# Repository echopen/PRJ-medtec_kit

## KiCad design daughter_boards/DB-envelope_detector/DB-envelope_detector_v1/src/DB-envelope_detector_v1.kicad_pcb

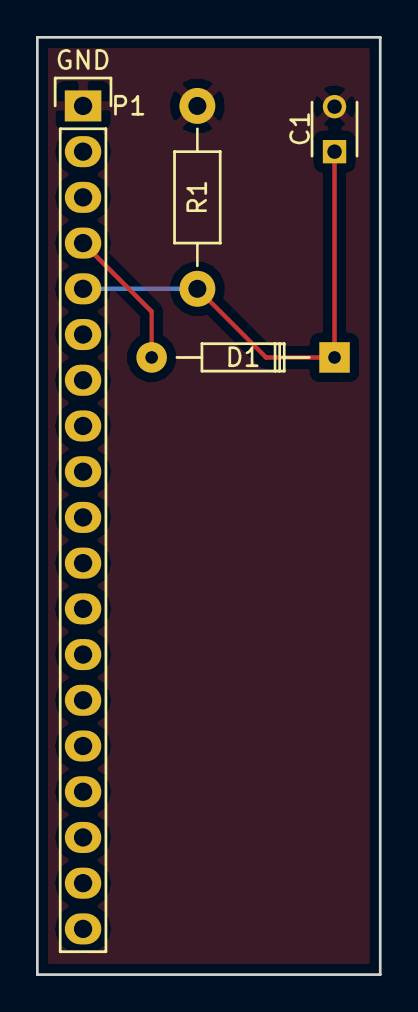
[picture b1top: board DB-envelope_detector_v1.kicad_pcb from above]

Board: 2 copper layers, 19.0 x 52.1 mm, 4 parts (0 on the bottom side), 3 nets.

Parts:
C1: 10p; C_Disc_D3_P2.5
D1: 1N60; Diode_DO-35_SOD27_Horizontal_RM10
P1: CONN_01X19; Header_pin_angled_1x19
R1: 3.9k; Resistor_Horizontal_RM10mm

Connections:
GND: C1.2, P1.1, R1.2
unnamed: C1.1, D1.1, P1.5, R1.1
unnamed: D1.2, P1.4

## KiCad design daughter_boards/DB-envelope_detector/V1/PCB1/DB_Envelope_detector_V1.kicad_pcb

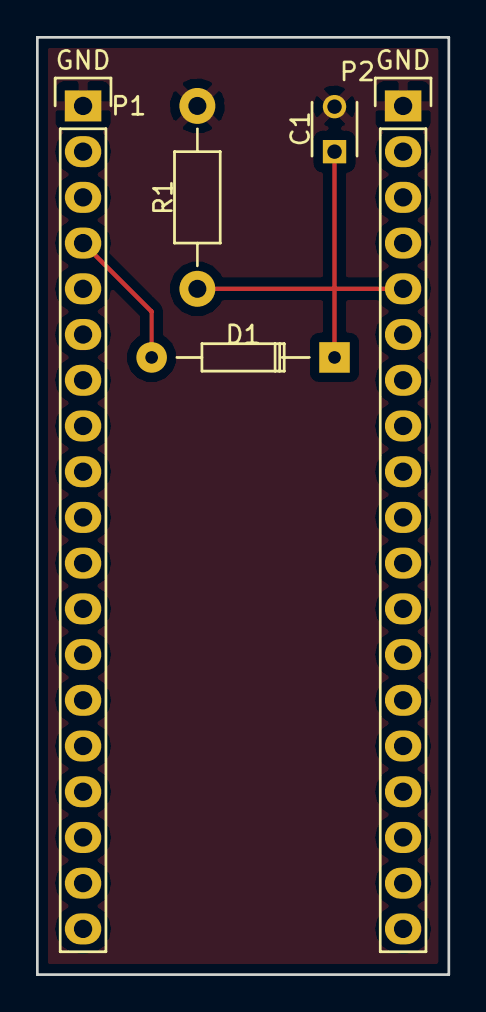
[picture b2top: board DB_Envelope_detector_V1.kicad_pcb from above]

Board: 2 copper layers, 22.9 x 52.1 mm, 5 parts (0 on the bottom side), 3 nets.

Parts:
C1: 10p; C_Disc_D3_P2.5
D1: 1N60; Diode_DO-35_SOD27_Horizontal_RM10
P1, P2: CONN_01X19; Header_pin_1x19
R1: 3.9k; Resistor_Horizontal_RM10mm

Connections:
GND: C1.2, P1.1, P2.1, R1.2
unnamed: C1.1, D1.1, P2.5, R1.1
unnamed: D1.2, P1.4

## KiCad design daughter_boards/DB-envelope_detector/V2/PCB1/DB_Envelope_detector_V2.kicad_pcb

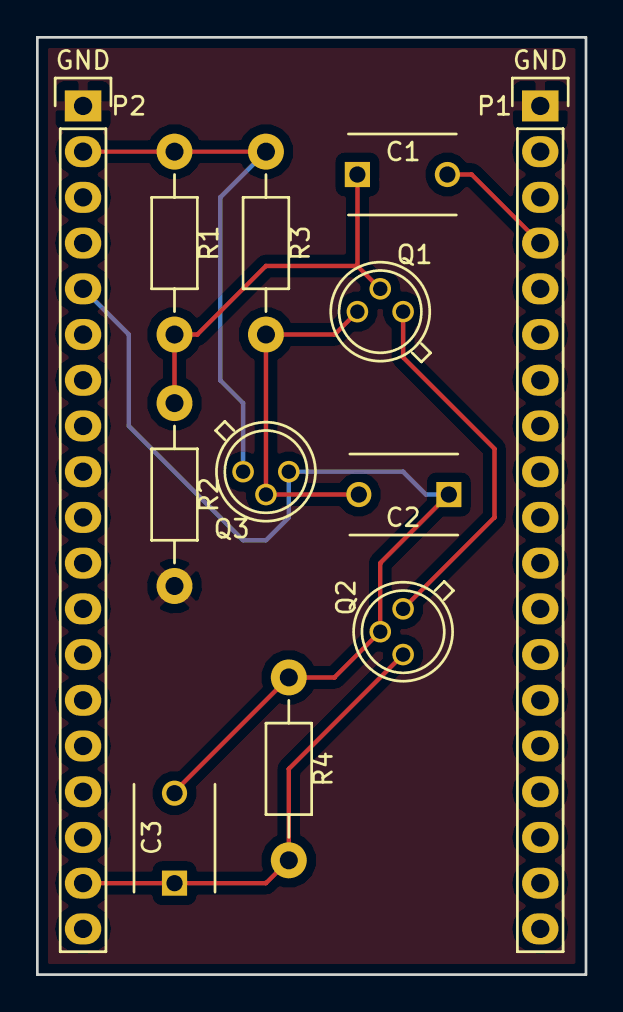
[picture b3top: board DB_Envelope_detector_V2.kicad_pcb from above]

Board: 2 copper layers, 30.5 x 52.1 mm, 12 parts (0 on the bottom side), 8 nets.

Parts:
C1: 10nF; C_Disc_D6_P5
C2: 1nF; C_Disc_D6_P5
C3: 33nF; C_Disc_D6_P5
P1, P2: CONN_01X19; Header_pin_1x19
Q1: 2N2222; TO-18_3Pin
Q2, Q3: 2N2907; TO-18_3Pin
R1: 2800; Resistor_Horizontal_RM10mm
R2: 1000; Resistor_Horizontal_RM10mm
R3, R4: 330; Resistor_Horizontal_RM10mm

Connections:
GND: P1.1, P2.1, R2.2
unnamed: C1.1, Q1.2, R1.2, R2.1
unnamed: C1.2, P1.4
unnamed: C2.1, C3.2, P2.5, Q2.2, Q3.3, R4.1
unnamed: C2.2, Q1.3, Q3.2, R3.2
unnamed: C3.1, P2.18, Q2.3, R4.2
unnamed: P2.2, Q3.1, R1.1, R3.1
unnamed: Q1.1, Q2.1

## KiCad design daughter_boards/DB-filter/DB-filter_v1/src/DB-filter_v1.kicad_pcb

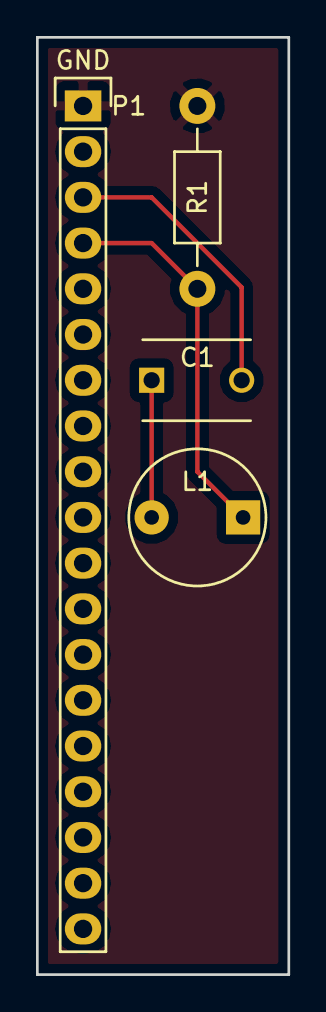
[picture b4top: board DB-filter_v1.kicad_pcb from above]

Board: 2 copper layers, 14.0 x 52.1 mm, 4 parts (0 on the bottom side), 4 nets.

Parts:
C1: 1n; C_TH_common
L1: 10u; INDUCTOR_V
P1: CONN_01X19; Header_pin_angled_1x19
R1: 330; Resistor_TH_common

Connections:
GND: P1.1, R1.2
unnamed: C1.1, L1.2
unnamed: C1.2, P1.3
unnamed: L1.1, P1.4, R1.1
